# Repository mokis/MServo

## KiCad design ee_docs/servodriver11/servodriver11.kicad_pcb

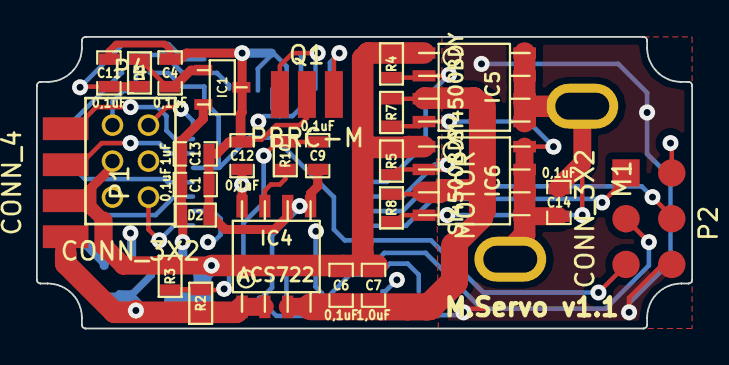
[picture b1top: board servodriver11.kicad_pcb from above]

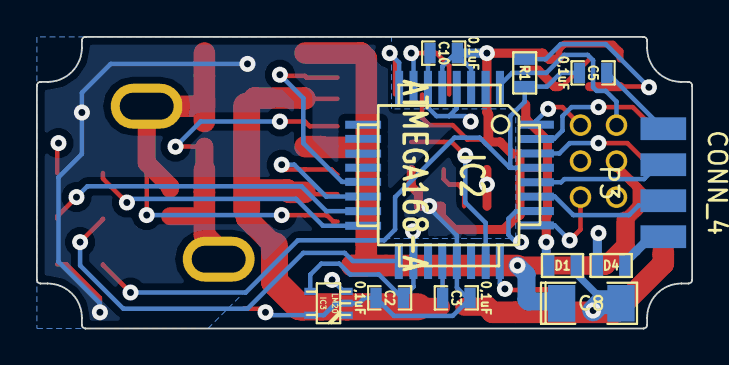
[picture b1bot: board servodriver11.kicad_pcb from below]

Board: 4 copper layers, 36.4 x 16.2 mm, 38 parts (11 on the bottom side), 30 nets.

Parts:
C1, C2, C3, C4, C5, C6, C9, C10, C11, C12, C14: 0,1uF; SM0603_Capa
C7: 1,0uF; SM0603_Capa
C8: 33uF; SM1206POL
C13: 1uF; SM0603_Capa
D1, D3, D4: DIODESCH; SM0603
D2: 15V; SM0603
IC1: LM3480; sot23
IC2: ATMEGA168-A; TQFP32
IC3: LM20; sc70-5
IC4: ACS722; so-8
IC5, IC6: SI4500BDY; so-8
M1: MOTOR; MOTOR1
P1: CONN_4; hirose_top
P2: CONN_3X2; PIN_2x3_SMD
P3: CONN_4; hirose_bottom
P4: CONN_3X2; 6pin_hirose
Q1: PBRC-M; PBRCM
R1: 10k; SM0603
R2: 5k6; SM0603
R3: 1k5; SM0603
R4, R5, R7, R8: 100k; SM0603
R10: 1k; SM0603

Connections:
+3.3V: C2.2, C10.2, C11.1, C12.1, D3.2, D4.2, IC2.4, IC2.6, IC2.18, IC3.4, IC4.8, P2.2, P4.3, R1.1
+8V: C8.2, D1.1, IC4.1, IC4.2, P1.1, R2.1
/CLK: IC2.1, P4.1
/CS: IC2.32, P4.6
/DTR: C5.2, P3.1
/MISO: IC2.16, P2.1
/MOSI: IC2.15, P2.4
/POSSENSE: IC2.25, P4.4
/RESET: C5.1, IC2.29, P2.5, R1.2
/RX: IC2.30, P1.3
/SCK: IC2.17, P2.3
/SCL: IC2.28, P3.2
/SDA: IC2.27, P3.3
/TEMPSENSE: IC2.26, IC3.3
/TX: IC2.31, P1.4
/VOLTSENSE: IC2.24, R2.2, R3.1
/motordriver/CSENSE: C9.1, IC2.23, R10.2
/motordriver/MA: IC2.13, IC5.2, R4.1
/motordriver/MB: IC2.14, IC6.2, R5.1
GND: C1.2, C2.1, C3.1, C4.2, C6.2, C7.2, C8.1, C9.2, C10.1, C11.2, C12.2, C13.2, D2.1, IC1.2, IC2.3, IC2.5, IC2.21, IC3.2, IC3.5, IC4.5, IC4.6, IC5.1, IC6.1, P1.2, P2.6, P4.2, P4.5, Q1.2, R3.2, R4.2, R5.2
unnamed: IC2.7, Q1.1
unnamed: IC2.8, Q1.3
unnamed: C3.2, IC2.20
unnamed: D4.1, P3.4
unnamed: C1.1, C13.1, D1.2, D2.2, IC1.3
unnamed: C4.1, D3.1, IC1.1
unnamed: C6.1, C7.1, IC4.3, IC4.4, IC5.3, IC6.3, R7.2, R8.1
unnamed: C14.1, IC5.5, IC5.6, IC5.7, IC5.8, IC6.4, M1.1, R8.2
unnamed: C14.2, IC5.4, IC6.5, IC6.6, IC6.7, IC6.8, M1.2, R7.1
unnamed: IC4.7, R10.1
